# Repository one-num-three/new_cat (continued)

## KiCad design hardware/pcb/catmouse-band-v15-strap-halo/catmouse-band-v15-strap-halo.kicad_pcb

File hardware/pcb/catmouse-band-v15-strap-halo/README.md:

# CatMouse Band V1.5 Strap-Halo / Velcro Lite 主板

本目录是主板工程评审版。用 KiCad 10 打开 `catmouse-band-v15-strap-halo.kicad_pro` 查看原理图、四层 1.00 mm 裸板设计、本地封装和 RF 规则区。机械结构基准与接口在 [EVT-A 机电变更](../../docs/Strap-Halo-EVT-A-机电变更.md)。`catmouse-band-v15` 是 40 × 46 mm 基线参考。

前翼使用主板 J5，后翼使用 J6。沿编号方向分别为 VLED、GND、DIN、DOUT。J5 的 DOUT 经 330 Ω 回到 J6 的 DIN，J6 的 4 脚悬空。座子使用 Hirose FH19C-4S-0.5SH(10)，底面为插舌接触面。磁吸、马达、电池仅在主板底面保留平焊盘。磁吸四线通过 [独立柔性转接](../catmouse-band-v15-pogo-flex/README.md) 接到底壳。

## 验证与投板状态

使用 KiCad 自带的 Python 和 `../verify_strap_halo.py` 可在当前保存版本上复跑 ERC、DRC、原理图一致性和固件物理引脚校验。报告同时检查固件的 10 个 `PIN_*`、USB D± 和 BOOT。

KiCad 10.0.8 的[审查汇总](review/audit.json)记录 ERC 0 项、原理图一致性差异 0 项、固件物理引脚 13/13 一致。PN532 裸露焊盘内有四颗 Ø0.20 mm 接地通孔，钻孔避开钢网开口。[DRC 报告](review/drc.json)记录其他规则违规 0 项和布线未连通 10 项。[物料评审表](review/BOM-review.csv)共 38 项，其中 21 项已有嘉立创目录候选，17 项待配料。[贴装坐标评审表](review/CPL-review.csv)包含顶面 74 个贴装位号。

当前待连通的网络包括 USB、NFC 时钟与发射链路、灯带栅极与回传、IO0 测试点和 IMU 地址脚。主板发板前须完成布线、NFC 弹片与天线尾带选型、USB 实际叠层和 RF 匹配。MCP73831 与 AP2112 保留为参考电源方案，充电温控、终止时的系统负载以及深睡电流须以实际电池和样机确认。生成脚本会重建基线，继续布线时请从已提交的 KiCad 工程打开。

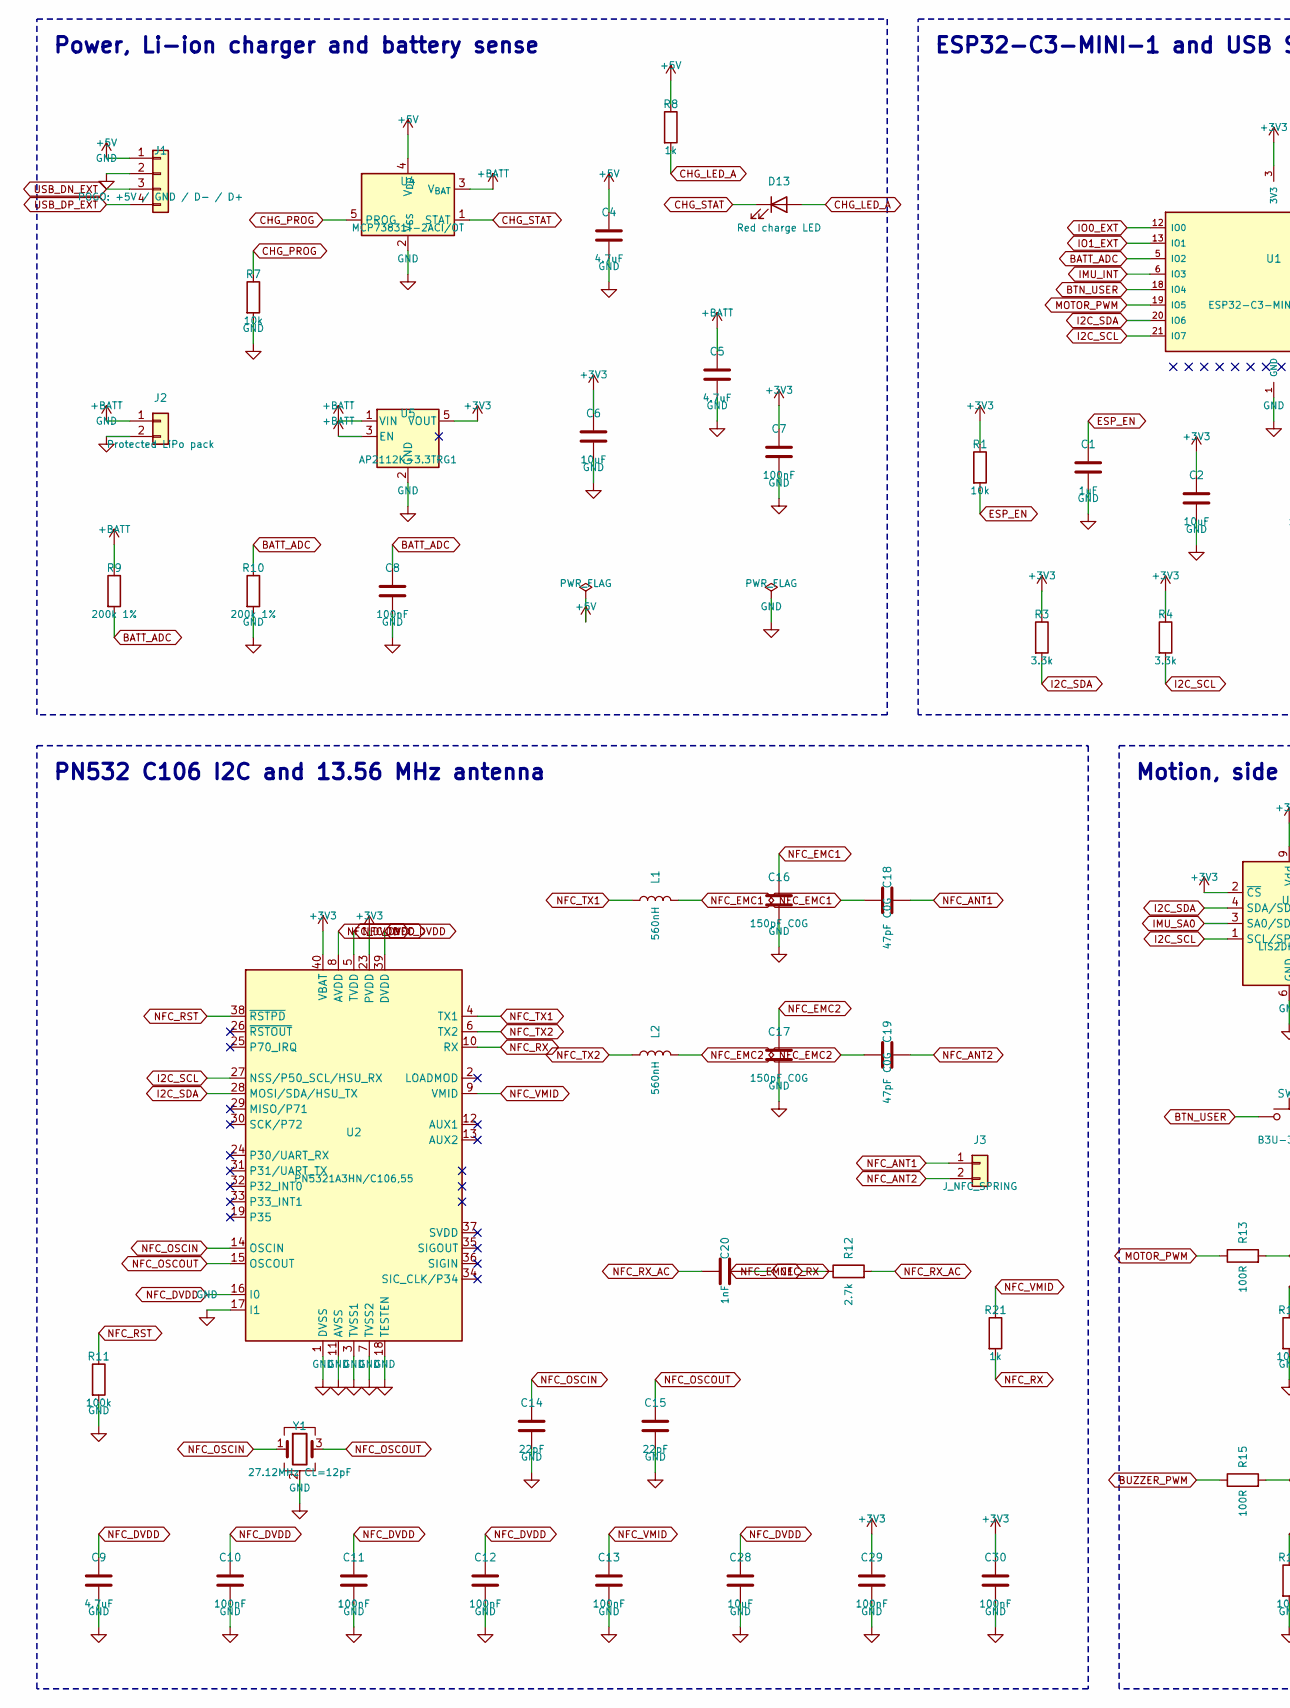
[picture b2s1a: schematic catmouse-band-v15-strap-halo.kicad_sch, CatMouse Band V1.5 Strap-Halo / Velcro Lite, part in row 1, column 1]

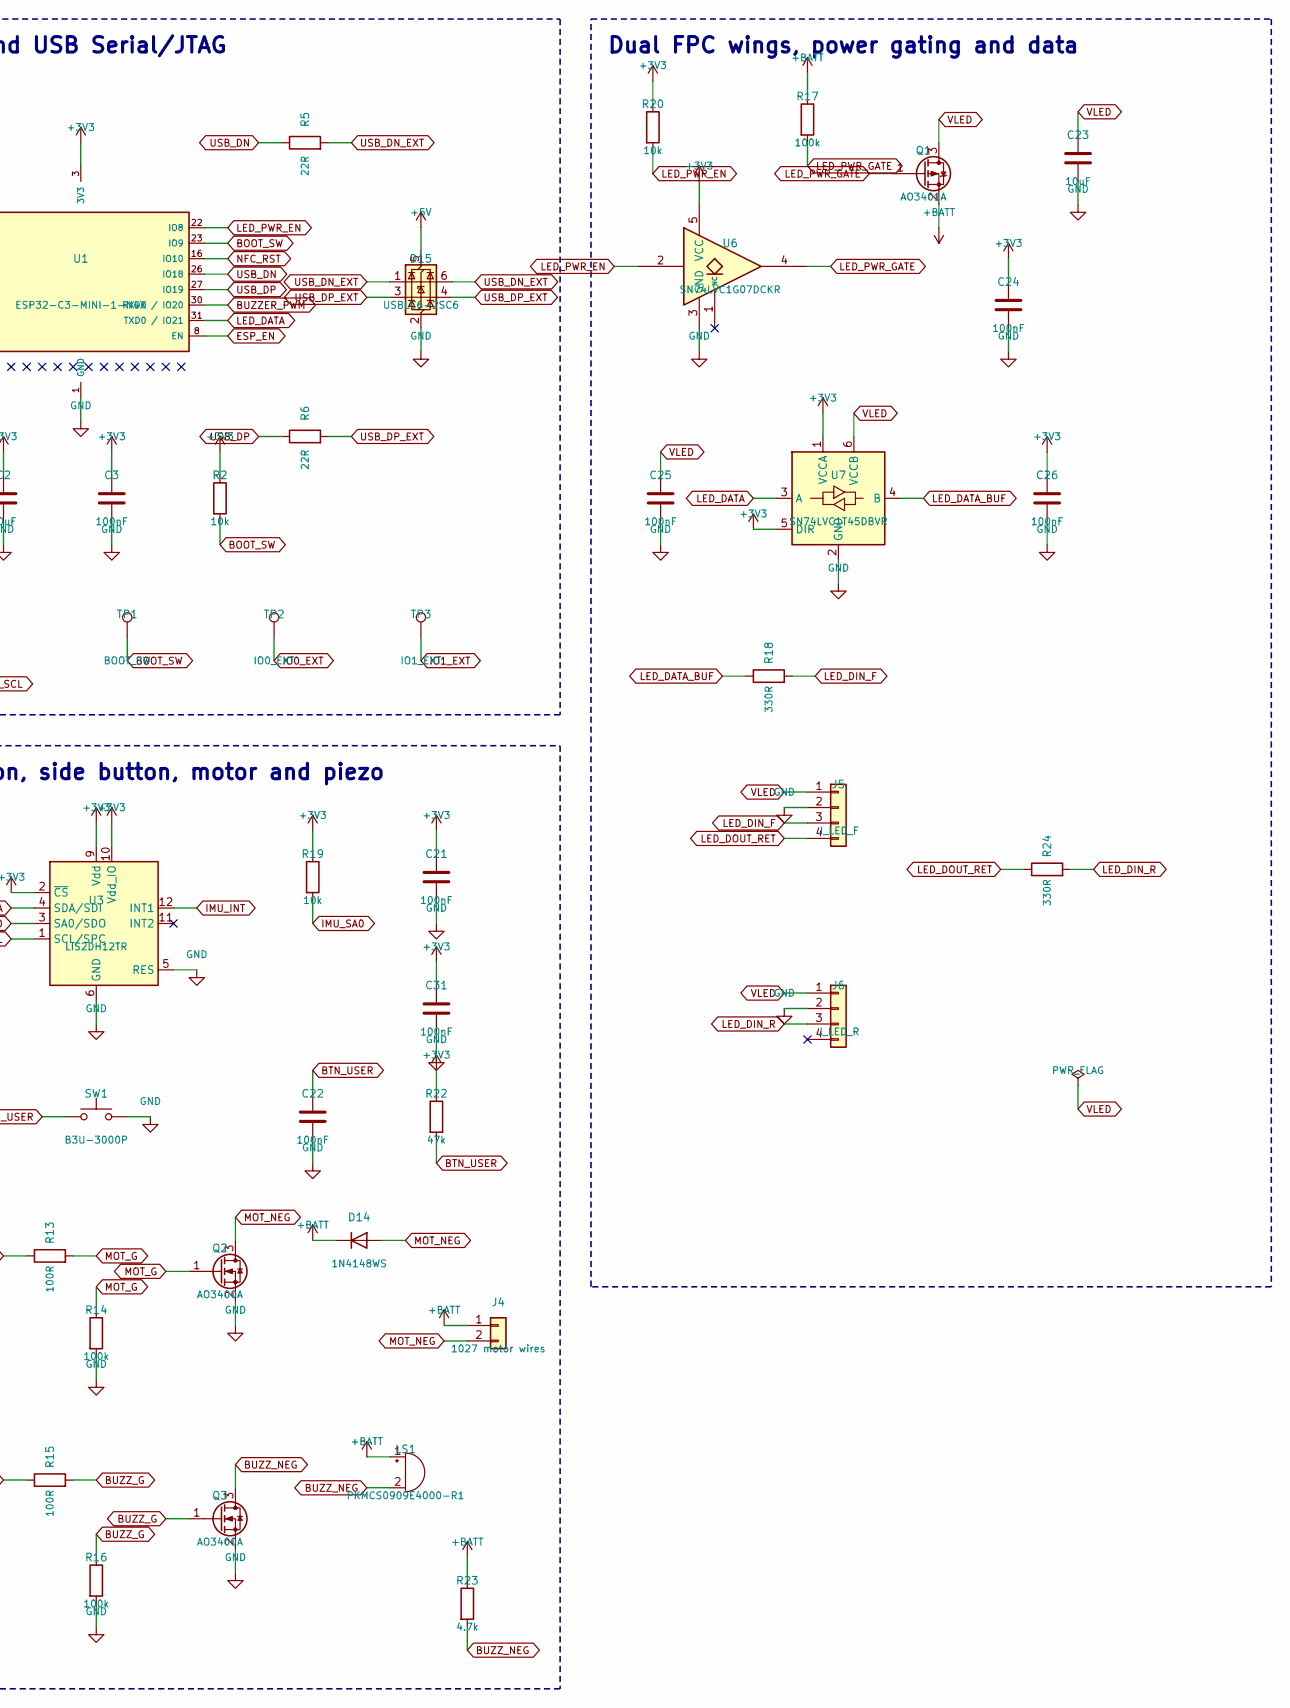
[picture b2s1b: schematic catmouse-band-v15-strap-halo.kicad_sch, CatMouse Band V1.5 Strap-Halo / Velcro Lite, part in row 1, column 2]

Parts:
C1: 1uF; C_0402_1005Metric; LCSC C5142580
C2, C6, C23: 10uF; C_0603_1608Metric; LCSC C193747
C3, C7, C8, C10, C11, C12, C13, C21, C22, C24, C25, C26, C29, C30, C31: 100nF; C_0402_1005Metric; LCSC C387958
C4, C5, C9: 4.7uF; C_0603_1608Metric; LCSC C7419425
C14, C15: 22pF; C_0402_1005Metric
C16, C17: 150pF C0G; C_0402_1005Metric; LCSC C541423
C18, C19: 47pF C0G; C_0402_1005Metric; LCSC C2169042
C20: 1nF; C_0402_1005Metric; LCSC C599568
C28: 10uF; C_0805_2012Metric; LCSC C669099
D13: Red charge LED; LED_0603_1608Metric; LCSC C2286
D14: 1N4148WS; D_SOD-323; LCSC C2128
D15: USBLC6-2SC6; SOT-23-6
J1: POGO: +5V / GND / D- / D+; Pogo_4x2.54_Flat
J2: Protected LiPo pack; Wire_Pads_2x2.54
J3: J_NFC_SPRING; NFC_Spring_2x2.00
J4: 1027 motor wires; Wire_Pads_2x2.54
J5: J_LED_F; FH19C-4S-0.5SH; LCSC C424650
J6: J_LED_R; FH19C-4S-0.5SH; LCSC C424650
L1, L2: 560nH; L_0603_1608Metric
LS1: PKMCS0909E4000-R1; Buzzer_Murata_PKMCS0909E; LCSC C910763
Q1: AO3401A; SOT-23; LCSC C15127
Q2, Q3: AO3400A; SOT-23; LCSC C20917
R1, R2, R7, R19, R20: 10k; R_0402_1005Metric
R3, R4: 3.3k; R_0402_1005Metric
R5, R6: 22R; R_0402_1005Metric
R8, R21: 1k; R_0402_1005Metric
R9, R10: 200k 1%; R_0402_1005Metric
R11, R14, R16, R17: 100k; R_0402_1005Metric
R12: 2.7k; R_0402_1005Metric
R13, R15: 100R; R_0402_1005Metric
R18, R24: 330R; R_0402_1005Metric
R22: 47k; R_0402_1005Metric
R23: 4.7k; R_0402_1005Metric
SW1: B3U-3000P; SW_SPST_B3U-3000P; LCSC C963349
TP1: BOOT_SW; TestPoint_Pad_D1.5mm
TP2: IO0_EXT; TestPoint_Pad_D1.5mm
TP3: IO1_EXT; TestPoint_Pad_D1.5mm
U1: ESP32-C3-MINI-1-N4X; ESP32-C3-MINI-1; LCSC C9900263492
U2: PN5321A3HN/C106,55; HVQFN-40-1EP_6x6mm_P0.5mm_EP4.1x4.1mm; LCSC C28925
U3: LIS2DH12TR; LGA-12_2x2mm_P0.5mm; LCSC C110926
U4: MCP73831T-2ACI/OT; SOT-23-5
U5: AP2112K-3.3TRG1; SOT-23-5; LCSC C51118
U6: SN74LVC1G07DCKR; SOT-353_SC-70-5; LCSC C7830
U7: SN74LVC1T45DBVR; SOT-23-6
Y1: 27.12MHz CL=12pF; Crystal_SMD_3225-4Pin_3.2x2.5mm

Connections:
+3V3: C2.1, C3.1, C6.1, C7.1, C21.1, C24.1, C26.1, C29.1, C30.1, C31.1, R1.1, R2.1, R3.1, R4.1, R19.1, R20.1, R22.1, U1.3 (3V3), U2.23 (PVDD), U2.40 (VBAT), U3.2 (~CS), U3.9 (Vdd), U3.10 (Vdd_IO), U5.5 (VOUT), U6.5 (VCC), U7.1 (VCCA), U7.5 (DIR)
+BATT: C5.1, D14.1 (K), J2.1, J4.1, LS1.1 (+), Q1.2 (S), R9.1, R17.1, R23.1, U4.3 (V_{BAT}), U5.1 (VIN), U5.3 (EN)
BATT_ADC: C8.1, R9.2, R10.1, U1.5 (IO2)
BOOT_SW: R2.2, TP1.1, U1.23 (IO9)
BTN_USER: C22.1, R22.2, SW1.1, U1.18 (IO4)
BUZZER_PWM: R15.1, U1.30 (RXD0 / IO20)
BUZZ_G: Q3.1 (G), R15.2, R16.1
BUZZ_NEG: LS1.2 (-), Q3.3 (D), R23.2
CHG_LED_A: D13.2 (A), R8.2
CHG_PROG: R7.1, U4.5 (PROG)
CHG_STAT: D13.1 (K), U4.1 (STAT)
ESP_EN: C1.1, R1.2, U1.8 (EN)
I2C_SCL: R4.2, U1.21 (IO7), U2.27 (NSS/P50_SCL/HSU_RX), U3.1 (SCL/SPC)
I2C_SDA: R3.2, U1.20 (IO6), U2.28 (MOSI/SDA/HSU_TX), U3.4 (SDA/SDI)
IMU_INT: U1.6 (IO3), U3.12 (INT1)
IMU_SA0: R19.2, U3.3 (SA0/SDO)
IO0_EXT: TP2.1, U1.12 (IO0)
IO1_EXT: TP3.1, U1.13 (IO1)
LED_DATA: U1.31 (TXD0 / IO21), U7.3 (A)
LED_DATA_BUF: R18.1, U7.4 (B)
LED_DIN_F: J5.3, R18.2
LED_DIN_R: J6.3, R24.2
LED_DOUT_RET: J5.4, R24.1
LED_PWR_EN: R20.2, U1.22 (IO8), U6.2
LED_PWR_GATE: Q1.1 (G), R17.2, U6.4
MOTOR_PWM: R13.1, U1.19 (IO5)
MOT_G: Q2.1 (G), R13.2, R14.1
MOT_NEG: D14.2 (A), J4.2, Q2.3 (D)
NFC_ANT1: C18.2, J3.1
NFC_ANT2: C19.2, J3.2
NFC_DVDD: C9.1, C10.1, C11.1, C12.1, C28.1, U2.5 (TVDD), U2.8 (AVDD), U2.16 (I0), U2.39 (DVDD)
NFC_EMC1: C16.1, C18.1, L1.2, R12.1
NFC_EMC2: C17.1, C19.1, L2.2
NFC_OSCIN: C14.1, U2.14 (OSCIN), Y1.1
NFC_OSCOUT: C15.1, U2.15 (OSCOUT), Y1.3
NFC_RST: R11.1, U1.16 (IO10), U2.38 (~RSTPD)
NFC_RX: C20.2, R21.2, U2.10 (RX)
NFC_RX_AC: C20.1, R12.2
NFC_TX1: L1.1, U2.4 (TX1)
NFC_TX2: L2.1, U2.6 (TX2)
NFC_VMID: C13.1, R21.1, U2.9 (VMID)
USB_DN: R5.1, U1.26 (IO18)
USB_DN_EXT: D15.1 (I/O1), D15.6 (I/O1), J1.3, R5.2
USB_DP: R6.1, U1.27 (IO19)
USB_DP_EXT: D15.3 (I/O2), D15.4 (I/O2), J1.4, R6.2

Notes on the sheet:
Power, Li-ion charger and battery sense
ESP32-C3-MINI-1 and USB Serial/JTAG
PN532 C106 I2C and 13.56 MHz antenna
Motion, side button, motor and piezo
Dual FPC wings, power gating and data

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
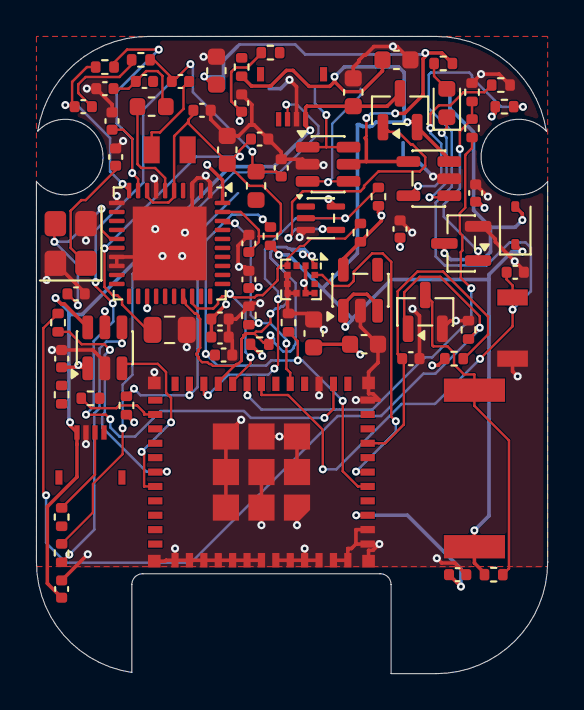
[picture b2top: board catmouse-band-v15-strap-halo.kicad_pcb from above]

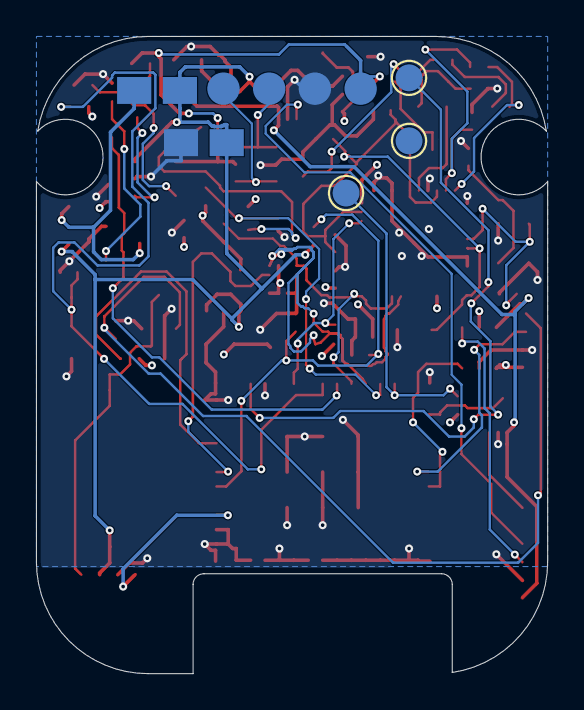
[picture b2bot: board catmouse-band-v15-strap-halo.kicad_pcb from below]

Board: 4 copper layers, 28.4 x 35.4 mm, 81 parts (6 on the bottom side), 48 nets.

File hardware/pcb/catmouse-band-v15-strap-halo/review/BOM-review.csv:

"Designator","Comment","Footprint","LCSC Part #","Quantity"
"C1","1uF","Capacitor_SMD:C_0402_1005Metric","C5142580","1"
"C2,C6,C23","10uF","Capacitor_SMD:C_0603_1608Metric","C193747","3"
"C3,C7,C8,C10,C11,C12,C13,C21,C22,C24,C25,C26,C29,C30,C31","100nF","Capacitor_SMD:C_0402_1005Metric","C387958","15"
"C4,C5,C9","4.7uF","Capacitor_SMD:C_0603_1608Metric","C7419425","3"
"C14,C15","22pF","Capacitor_SMD:C_0402_1005Metric","","2"
"C16,C17","150pF C0G","Capacitor_SMD:C_0402_1005Metric","C541423","2"
"C18,C19","47pF C0G","Capacitor_SMD:C_0402_1005Metric","C2169042","2"
"C20","1nF","Capacitor_SMD:C_0402_1005Metric","C599568","1"
"C28","10uF","Capacitor_SMD:C_0805_2012Metric","C669099","1"
"D13","Red charge LED","LED_SMD:LED_0603_1608Metric","C2286","1"
"D14","1N4148WS","Diode_SMD:D_SOD-323","C2128","1"
"D15","USBLC6-2SC6","Package_TO_SOT_SMD:SOT-23-6","","1"
"J5","J_LED_F","CatMouse_StrapHalo:FH19C-4S-0.5SH","C424650","1"
"J6","J_LED_R","CatMouse_StrapHalo:FH19C-4S-0.5SH","C424650","1"
"L1,L2","560nH","Inductor_SMD:L_0603_1608Metric","","2"
"LS1","PKMCS0909E4000-R1","CatMouse_StrapHalo:Buzzer_Murata_PKMCS0909E","C910763","1"
"Q1","AO3401A","Package_TO_SOT_SMD:SOT-23","C15127","1"
"Q2,Q3","AO3400A","Package_TO_SOT_SMD:SOT-23","C20917","2"
"R1,R2,R7,R19,R20","10k","Resistor_SMD:R_0402_1005Metric","","5"
"R3,R4","3.3k","Resistor_SMD:R_0402_1005Metric","","2"
"R5,R6","22R","Resistor_SMD:R_0402_1005Metric","","2"
"R8,R21","1k","Resistor_SMD:R_0402_1005Metric","","2"
"R9,R10","200k 1%","Resistor_SMD:R_0402_1005Metric","","2"
"R11,R14,R16,R17","100k","Resistor_SMD:R_0402_1005Metric","","4"
"R12","2.7k","Resistor_SMD:R_0402_1005Metric","","1"
"R13,R15","100R","Resistor_SMD:R_0402_1005Metric","","2"
"R18,R24","330R","Resistor_SMD:R_0402_1005Metric","","2"
"R22","47k","Resistor_SMD:R_0402_1005Metric","","1"
"R23","4.7k","Resistor_SMD:R_0402_1005Metric","","1"
"SW1","B3U-3000P","CatMouse_StrapHalo:SW_SPST_B3U-3000P","C963349","1"
"U1","ESP32-C3-MINI-1-N4X","CatMouse_StrapHalo:ESP32-C3-MINI-1","C9900263492","1"
"U2","PN5321A3HN/C106,55","Package_DFN_QFN:HVQFN-40-1EP_6x6mm_P0.5mm_EP4.1x4.1mm","C28925","1"
"U3","LIS2DH12TR","Package_LGA:LGA-12_2x2mm_P0.5mm","C110926","1"
"U4","MCP73831T-2ACI/OT","CatMouse_StrapHalo:SOT-23-5","","1"
"U5","AP2112K-3.3TRG1","Package_TO_SOT_SMD:SOT-23-5","C51118","1"
"U6","SN74LVC1G07DCKR","Package_TO_SOT_SMD:SOT-353_SC-70-5","C7830","1"
"U7","SN74LVC1T45DBVR","Package_TO_SOT_SMD:SOT-23-6","","1"
"Y1","27.12MHz CL=12pF","Crystal:Crystal_SMD_3225-4Pin_3.2x2.5mm","","1"

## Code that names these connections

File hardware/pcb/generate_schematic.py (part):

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    sch.place_part("Device", "C", "C6", "10uF", "Capacitor_SMD:C_0603_1608Metric", 104.14, 88.9, 0, {"1": "+3V3", "2": "GND"})
    sch.place_part("Device", "C", "C7", "100nF", "Capacitor_SMD:C_0402_1005Metric", 119.38, 88.9, 0, {"1": "+3V3", "2": "GND"})

    # 电池精密分压采样 (200k + 200k + 100nF -> GPIO2 BATT_ADC)
    sch.place_part("Device", "R", "R9", "200k 1%", "Resistor_SMD:R_0402_1005Metric", 53.34, 114.3, 0, {"1": "+BATT", "2": "BATT_ADC"})
    sch.place_part("Device", "R", "R10", "200k 1%", "Resistor_SMD:R_0402_1005Metric", 76.2, 114.3, 0, {"1": "BATT_ADC", "2": "GND"})
    sch.place_part("Device", "C", "C8", "100nF", "Capacitor_SMD:C_0402_1005Metric", 99.06, 114.3, 0, {"1": "BATT_ADC", "2": "GND"})
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        {
            "1": "+3V3",
            "2": "ESP_EN",
            "3": "BTN_USER",      # GPIO4 (RTC唤醒)
            "4": "MOTOR_PWM",     # GPIO5
            "5": "I2C_SDA",       # GPIO6
            "6": "I2C_SCL",       # GPIO7
            "7": "LED_PWR_EN",    # GPIO8 (启动高电平 = 默认关闭灯环PMOS!)
            "8": "BOOT_SW",       # GPIO9
            "9": "GND",
            "10": "NFC_RST",      # GPIO10
            "11": "BUZZER_PWM",   # GPIO20
            "12": "LED_DATA",     # GPIO21
            "13": "USB_DN",       # GPIO18
            "14": "USB_DP",       # GPIO19
            "15": "IMU_INT",      # GPIO3 (RTC唤醒)
            "16": "BATT_ADC",     # GPIO2 (ADC1)
            "17": "IO1_EXT",      # GPIO1 预留扩展
            "18": "IO0_EXT",      # GPIO0 预留扩展
            "19": "GND",
        },
        stub_len=5.08,
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
    # VLED 经过 PMOS 漏极(passive)，挂一个 PWR_FLAG 声明为有效供电网络供 WS2812B power_in 检查！
    sch.add_power("PWR_FLAG", 398.78, 48.26, 0)
    sch.add_global_label("VLED", 398.78, 48.26, 0)

    # 12 颗 WS2812B-2020 菊花链（4 行 × 3 列整洁排布）
    for i in range(12):
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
